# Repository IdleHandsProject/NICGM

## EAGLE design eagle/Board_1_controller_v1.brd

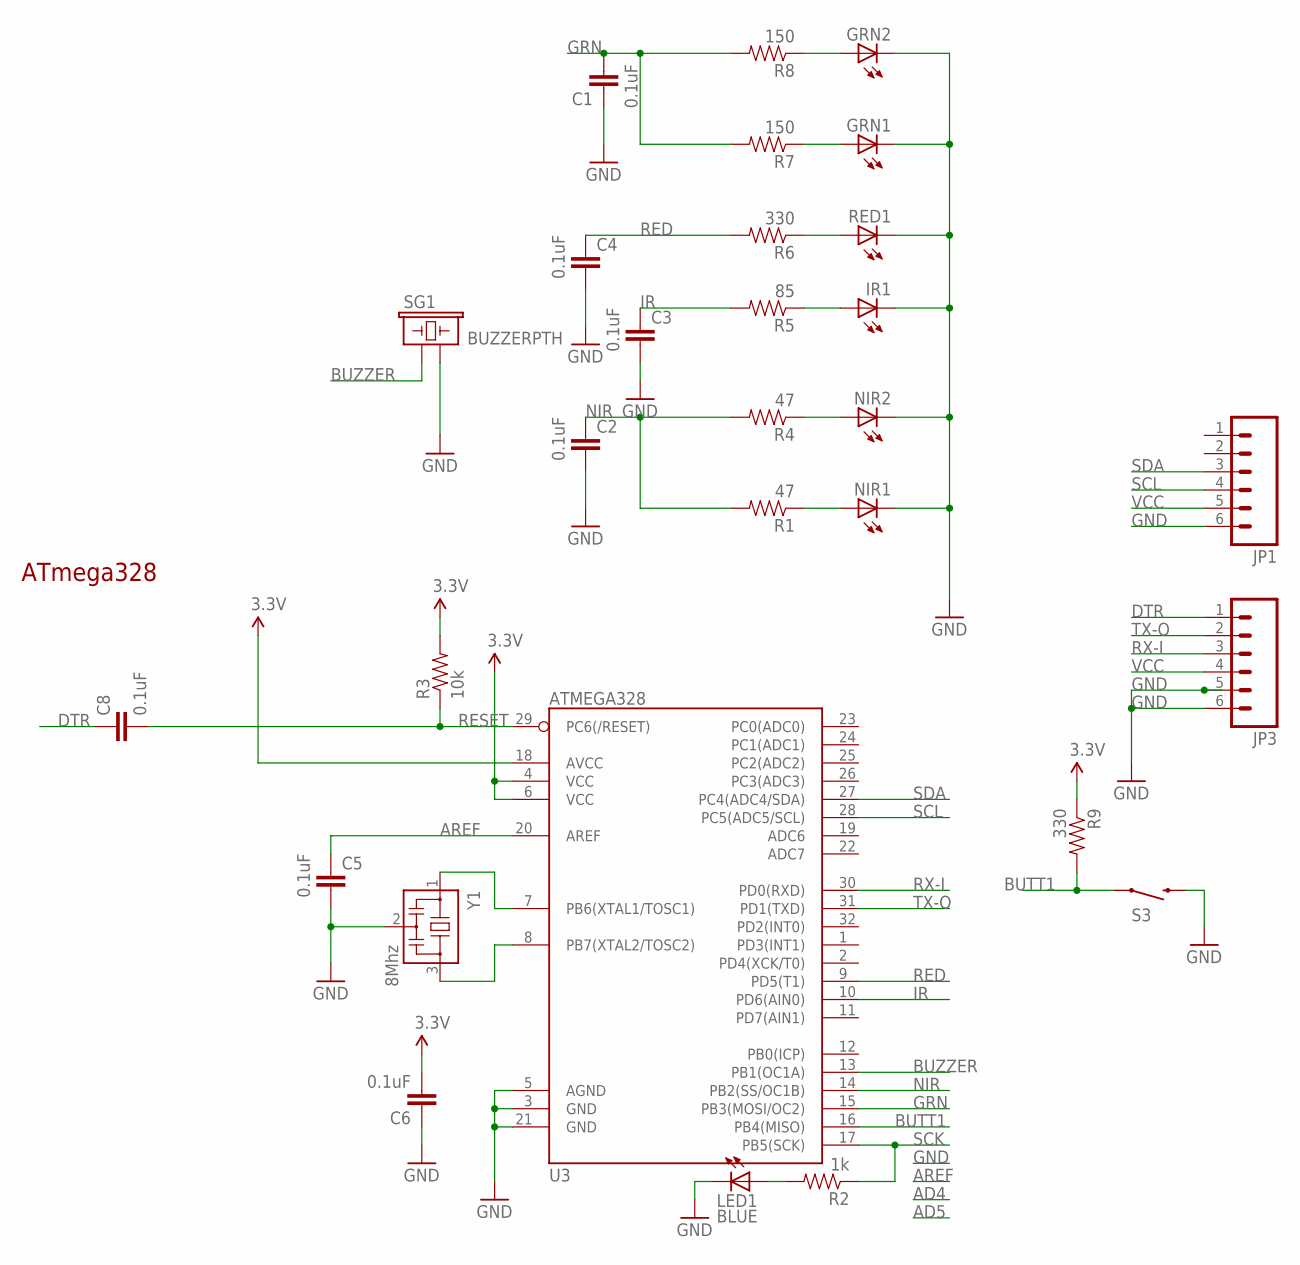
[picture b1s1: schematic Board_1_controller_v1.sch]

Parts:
C1, C2, C3, C4, C5, C6, C8: 0.1uF; 0402-CAP
GRN1, GRN2: LED0603; LED-0603
IR1: LED0603; LED-0603
JP1, JP3: M06SMD-1MM; 1X06-1MM
LED1: BLUE; LED-0603
NIR1, NIR2: LEDLED1550; 1210
R1, R4: 47; 0402-RES
R2: 1k; 0402-RES
R3: 10k; 0402-RES
R5: 85; 0402-RES
R6, R9: 330; 0402-RES
R7, R8: 150; 0402-RES
RED1: LED0603; LED-0603
S3: SWITCH-MOMENTARY-2-SMD-1101NE; TACTILE-SWITCH-1101NE
SG1: BUZZERPTH; BUZZER-12MM
U3: ATMEGA328; TQFP32-08
Y1: 8Mhz; CSTCR6M

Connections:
AREF: C5.1, U3.20 (AREF)
BUTT1: R9.2, S3.P$1 (1), U3.16 (PB4(MISO))
BUZZER: SG1.+ (1), U3.13 (PB1(OC1A))
DTR: C8.1, JP3.1
GND: C1.1, C2.2, C3.2, C4.2, C5.2, C6.1, GRN1.C, GRN2.C, IR1.C, JP1.6, JP3.5, JP3.6, LED1.C, NIR1.2 (C), NIR2.2 (C), RED1.C, S3.P$2 (2), SG1.- (2), U3.3 (GND), U3.5 (AGND), U3.21 (GND), Y1.2
GRN: C1.2, R7.2, R8.2, U3.15 (PB3(MOSI/OC2))
IR: C3.1, R5.2, U3.10 (PD6(AIN0))
unnamed: LED1.A, R2.2
unnamed: U3.7 (PB6(XTAL1/TOSC1)), Y1.1
unnamed: U3.8 (PB7(XTAL2/TOSC2)), Y1.3
unnamed: GRN2.A, R8.1
unnamed: GRN1.A, R7.1
unnamed: R6.1, RED1.A
unnamed: IR1.A, R5.1
unnamed: NIR2.1 (A), R4.1
unnamed: NIR1.1 (A), R1.1
NIR: C2.1, R1.2, R4.2, U3.14 (PB2(SS/OC1B))
RED: C4.1, R6.2, U3.9 (PD5(T1))
RESET: C8.2, R3.1, U3.29 (PC6(/RESET))
RX-I: JP3.3, U3.30 (PD0(RXD))
SCK: R2.1, U3.17 (PB5(SCK))
SCL: JP1.4, U3.28 (PC5(ADC5/SCL))
SDA: JP1.3, U3.27 (PC4(ADC4/SDA))
TX-O: JP3.2, U3.31 (PD1(TXD))
VCC: C6.2, JP1.5, JP3.4, R3.2, R9.1, U3.4 (VCC), U3.6 (VCC), U3.18 (AVCC)

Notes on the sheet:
ATmega328

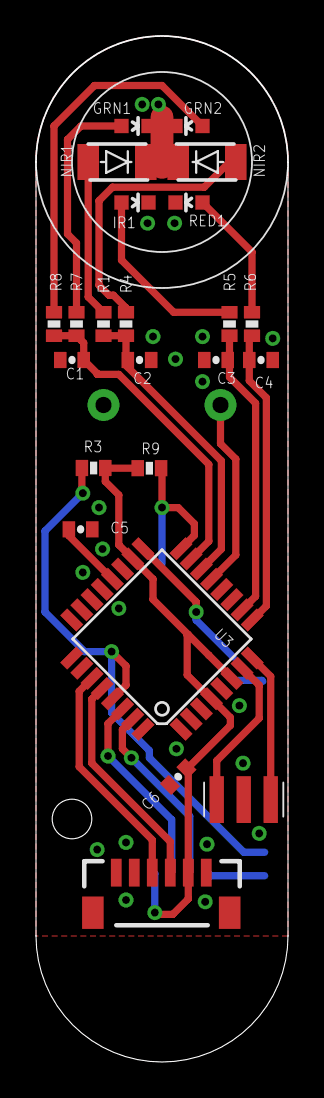
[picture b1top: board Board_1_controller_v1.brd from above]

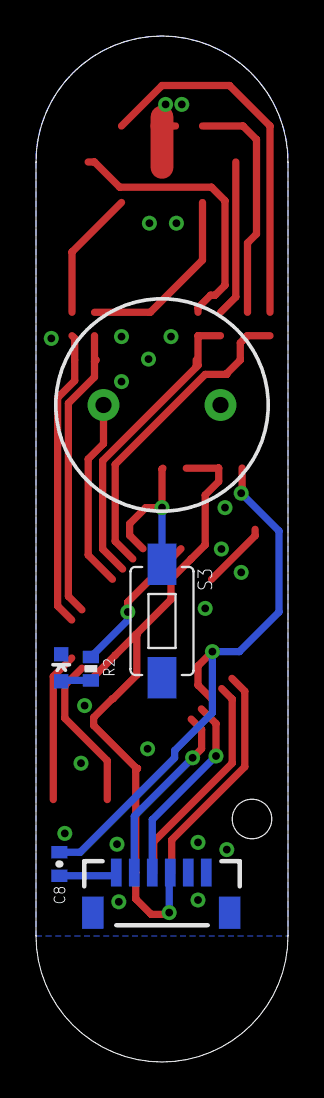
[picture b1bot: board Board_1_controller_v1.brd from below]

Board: 2 copper layers, 14.0 x 57.0 mm, 29 parts (6 on the bottom side), 25 nets.

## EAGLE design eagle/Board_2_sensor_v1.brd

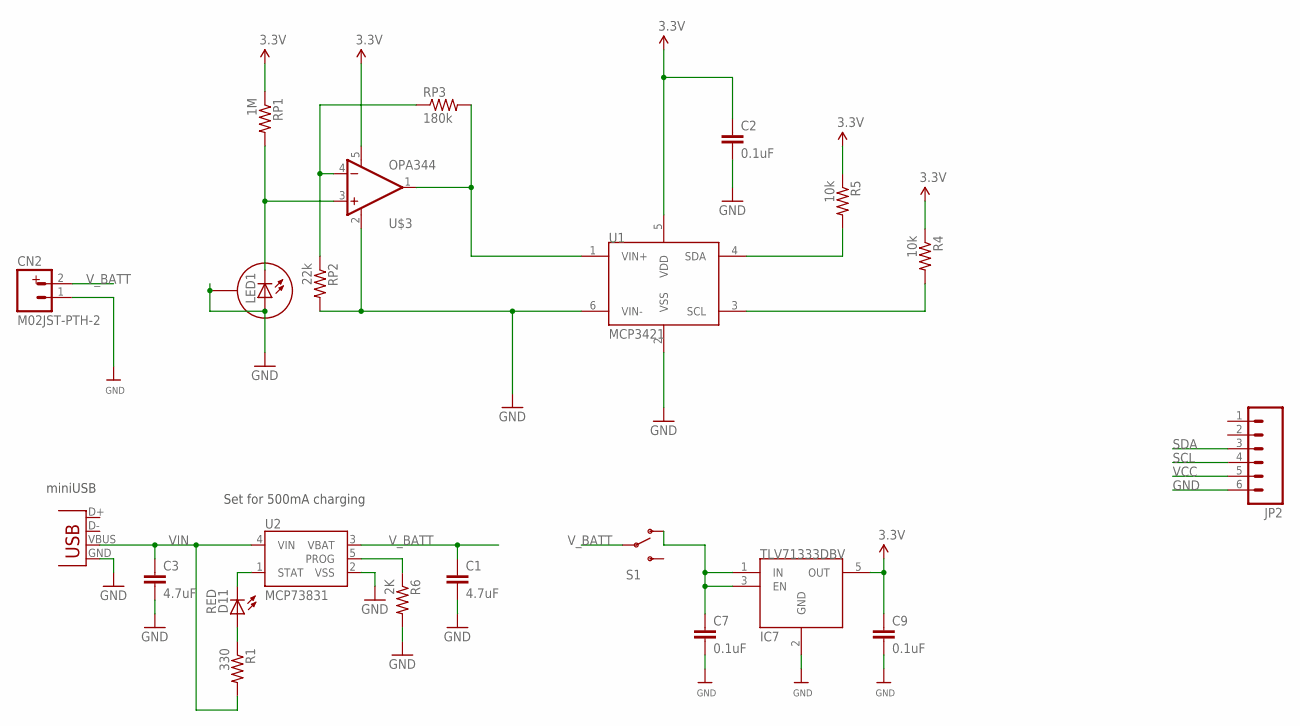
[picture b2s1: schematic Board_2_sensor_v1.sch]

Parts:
C1, C3: 4.7uF; 0402-CAP
C2: 0.1uF; 0402-CAP
C7, C9: 0.1uF; C0402
CN2: M02JST-PTH-2; JST-2-PTH
D11: RED; LED-0603
IC7: TLV71333DBV; SOT-23-5
JP2: M06SMD-1MM; 1X06-1MM
LED1: MTPD1346; TO-46
R1: 330; 0402-RES
R4, R5: 10k; 0402-RES
R6: 2K; 0402-RES
RP1: 1M; 0402-RES
RP2: 22k; 0402-RES
RP3: 180k; 0402-RES
S1: SWITCH-SPDTSMD; AYZ0202
U1: MCP3421; SOT-23-6
U2: MCP73831; SOT23-5
U$3: OPA344; SOT23-5
X1: Micro USB; USB-MICROB

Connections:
GND: C1.2, C2.2, C3.2, C7.2, C9.2, CN2.1, IC7.2 (GND), JP2.6, LED1.C, LED1.CASE, R6.2, RP2.2, U1.2 (VSS), U1.6 (VIN-), U2.2 (VSS), U$3.2 (V-), X1.GND
unnamed: LED1.A, RP1.2, U$3.3 (+IN)
unnamed: RP2.1, RP3.1, U$3.4 (-IN)
unnamed: RP3.2, U1.1 (VIN+), U$3.1 (OUT)
unnamed: C7.1, IC7.1 (IN), IC7.3 (EN), S1.1 (O)
unnamed: D11.A, R1.1
PROG: R6.1, U2.5 (PROG)
SCL: JP2.4, R4.2, U1.3 (SCL)
SDA: JP2.3, R5.2, U1.4 (SDA)
STAT: D11.C, U2.1 (STAT)
VCC: C2.1, C9.1, IC7.5 (OUT), JP2.5, R4.1, R5.1, RP1.1, U1.5 (VDD), U$3.5 (V+)
VIN: C3.1, R1.2, U2.4 (VIN), X1.VBUS
V_BATT: C1.1, CN2.2, S1.2, U2.3 (VBAT)

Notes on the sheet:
Set for 500mA charging
miniUSB

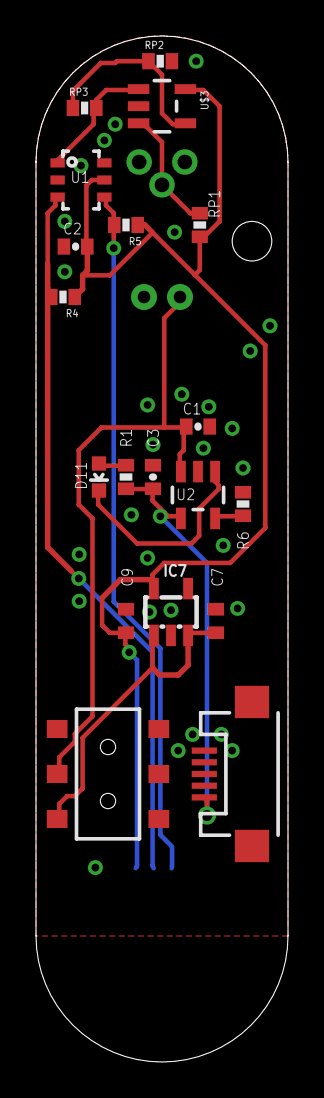
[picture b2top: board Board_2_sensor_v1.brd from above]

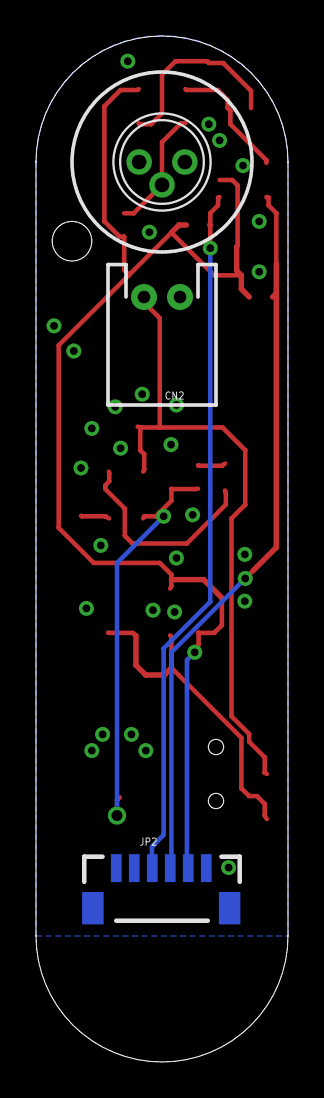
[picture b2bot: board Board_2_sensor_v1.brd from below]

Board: 2 copper layers, 14.0 x 57.0 mm, 22 parts (3 on the bottom side), 13 nets.

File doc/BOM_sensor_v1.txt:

"Part";"Value";"Device";"Package";"Description";"PROD_ID";
"C1";"4.7uF";"CAP0402-CAP";"0402-CAP";"Capacitor";"";
"C2";"0.1uF";"CAP0402-CAP";"0402-CAP";"Capacitor";"";
"C3";"4.7uF";"CAP0402-CAP";"0402-CAP";"Capacitor";"";
"C7";"0.1uF";"C-EUC0402";"C0402";"CAPACITOR, European symbol";"";
"C9";"0.1uF";"C-EUC0402";"C0402";"CAPACITOR, European symbol";"";
"CN2";"M02JST-PTH-2";"M02JST-PTH-2";"JST-2-PTH";"Standard 2-pin 0.1" header. Use with";"";
"D11";"RED";"LED0603";"LED-0603";"LEDs";"";
"IC7";"TLV71333DBV";"TLV71333DBV";"SOT-23-5";"Capacitor-Free, 150-mA, Low-Dropout Regulator";"";
"JP2";"";"M06SMD-1MM";"1X06-1MM";"Header 6";"";
"L1";"";"INDUCTOR0402";"C0402";"Inductors";"";
"LED1";"";"MTPD1346";"TO-46";"LEDs";"";
"R1";"330";"RESISTOR0402-RES";"0402-RES";"Resistor";"";
"R4";"10k";"RESISTOR0402-RES";"0402-RES";"Resistor";"";
"R5";"10k";"RESISTOR0402-RES";"0402-RES";"Resistor";"";
"R6";"2K";"RESISTOR0402-RES";"0402-RES";"Resistor";"";
"RP1";"1M";"RESISTOR0402-RES";"0402-RES";"Resistor";"";
"S1";"";"SWITCH-SPDTSMD";"AYZ0202";"SPDT Switch";"SWCH-08179";
"U1";"MCP3421";"MCP3421";"SOT-23-6";"18-Bit Analog-to-Digital Converter";"";
"U2";"MCP73831";"MCP73831";"SOT23-5";"Microchip's MCP73831";"";
"X1";"Micro USB";"USB-MICROB";"USB-MICROB";"USB Connectors";"";

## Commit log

2014-09-22 initial upload
2014-09-29 cad finish and boards updated
2014-10-18 Latest Update, research files added
2014-10-18 Added PDF Files

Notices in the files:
parts and their libraries:
SparkFun-Connectors: Licensing: CC v3.0 Share-Alike You are welcome to use this library for commercial purposes.
